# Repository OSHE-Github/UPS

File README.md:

# UPS

Uninterruptible Power Supply Hat for Raspberry Pi

This is still very early in the design phase and is not suitable for use.

*･゜ﾟ･*:.｡..｡.:*･'(*ﾟ▽ﾟ*)'･*:.｡. .｡.:*･゜ﾟ･*

## Copyright

- All code is licensed under the GPL 3.0 or later. You can view a copy of this license in LICENSE.code
- All hardware computer aided design "CAD files" are licensed under the CERN-OHL-S license. A copy of this license can be found in LICENSE.cad
- Some footprints are provided by the manufacturer or a third party source. They are licensed under their respective licenses.

Which licenses apply to which files will be clarified in a later commit. If you have questions please contact us.

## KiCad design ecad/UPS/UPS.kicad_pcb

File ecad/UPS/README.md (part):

## Current and thermal review - 2026-10-20

**The current board is not qualified for continuous 5 A USB output.** Two specified parts lack margin, and a single via carries the entire boost-input current. No PCB or firmware changes were made during this review.

The user confirmed the [GST36U12-P1J adapter](https://www.meanwell.com/Upload/PDF/GST36U/GST36U-SPEC.PDF): 12 V, 3 A, 36 W. Battery model remains unknown. The 5 A load is a review scenario, not a confirmed requirement. Calculations use the fitted boost divider's nominal 5.0895 V, 150 mA of provisional auxiliary load, 90% boost efficiency and 93% charger-stage efficiency. Efficiencies and auxiliary current must be measured. Voltages below refer to the boost input; battery-terminal voltage must be higher by the upstream drop. Four cells share current only approximately.

| Boost input | Input current at 3 A USB | Input current at 5 A USB |
| --- | ---: | ---: |
| 4.2 V | 4.24 A | 6.93 A |
| 3.7 V | 4.81 A | 7.87 A |
| 3.3 V | 5.40 A | 8.83 A |
| 3.0 V | 5.94 A | 9.71 A |

### Changes to prioritize

1. **R38:** the BOM's [RCL1218 jumper](https://www.vishay.com/docs/20046/rcle3.pdf) is rated 7 A, with resistance up to 20 milliohms. The 5 A USB scenario exceeds that at low battery. At 9.71 A, its resistance bound corresponds to 1.88 W; this is a sensitivity bound, not a measured loss. Replace it with a suitably rated low-resistance link or designed copper connection. Do not simply assume zero ohms means unlimited current.
2. **R38 copper escape:** a native connectivity experiment confirms that removing the single via at (133, 73) mm disconnects R38.1 from L2.1. Its drill is 0.3 mm, and its front trace is 0.8 mm wide / 1.4375 mm long. Provide a broad connection and a distributed via array when redesigning this feed. The other ten VIN vias do not bypass this bottleneck. [Evidence](review/current-path-bottleneck.json).
3. **F2:** the [MF-USML550/12](https://www.bourns.com/docs/product-datasheets/mf-usml-x.pdf) holds 5.5 A at 23 C, 4.68 A at 40 C, 4.15 A at 50 C and 3.6 A at 60 C. It carries USB plus auxiliary current. A 5 A USB load therefore lacks hot-enclosure margin. Select protection by hot hold-current, fault behavior and downstream ratings together; simply fitting a larger fuse is not a complete fix. F1 is also only 12 V rated, requiring voltage-margin review on the nominal 12 V adapter input.

### Where heat is likely

| Part / path | Calculation or observation | Review consequence |
| --- | --- | --- |
| R17 battery shunt | 0.94 W at 9.71 A with schematic 10 milliohms; 0.12 W with BOM 1.3 milliohms | Resolve the actual resistance, rating and footprint; these alternatives also change current measurement/control. |
| L2 boost inductor | About 0.51 W copper loss at 9.71 A using maximum 20 C DCR, before core loss and hot-resistance increase | Its published 16.8 A / 40 K-rise and 24.7 A / 30%-inductance-drop figures suggest current headroom; actual PCB temperature still needs testing. [Panasonic](https://na.industrial.panasonic.com/products/inductors-coils/surface-mount-power-inductors/lineup/power-inductors-automotive-applications/series/57509/model/70593). |
| PS1 boost stage | 2.91 W total converter loss at 90% efficiency, versus 1.38 W at 95%, at the provisional 5 A load | This includes L2 and other converter losses; it is not all IC heat. Do not add L2 loss to it again. |
| Q4 battery FET | At 9.71 A, every 10 milliohms produces 0.94 W | Its resistance needs actual gate drive and hot-junction characterization. The FDS6681Z guarantees quoted on-resistance at -4.5/-10 V gate drive; do not assume those numbers at low 1S voltage. [onsemi](https://www.onsemi.com/download/data-sheet/pdf/fds6681z-d.pdf). |
| Q3 USB switch | 5 A through 4 milliohms is 0.10 W at the datasheet's 4.5 V gate-drive condition | Verify gate overdrive and hot resistance; not currently the leading estimated heater. [Infineon](https://www.infineon.com/assets/row/public/documents/24/49/infineon-irlr7843-datasheet-en.pdf). |
| L1 charger inductor | Published 12 A RMS at 40 C rise, 27 A saturation criterion, 7 milliohm maximum DCR | It carries system current plus charge current on adapter power. A 36 W / 93% / 3 V limiting scenario is 11.16 A and about 0.87 W DC copper loss before ripple/core loss. Use actual VSYS setting, not battery voltage, for final sizing. Footprint compatibility remains unresolved. [Bourns](https://www.bourns.com/docs/product-datasheets/srp1038a.pdf). |

At the 5 A scenario, the adapter supplies approximately **2.61 A before charging**, leaving an upper estimate of **4.36 W** on the system rail for charging, before charge-path loss and design reserve. That is about 1 A charging near 4.2 V. Charge-current control must yield to the 3 A input limit. The firmware inspected currently handles battery voltage and fan control; this review did not find a complete charging/temperature-shutdown policy in the production main loop.

### Temperature and copper limits

The [TPS61288 datasheet](https://www.ti.com/lit/ds/symlink/tps61288.pdf) specifies a 125 C recommended junction maximum and reports 33.6 C/W on its EVM versus 71.4 C/W on its standard test board. At 40 C ambient and 1 W IC dissipation these give 74 C versus 111 C; at 1.5 W they give 90 C versus 147 C. These are sensitivity examples, not predictions for this PCB or certification of the selected L variant. The 15 A headline is peak switch current, not available USB output current; its current-limit table is characterized under different voltage conditions.

The saved stackup specifies approximately 2 oz outer copper and 0.5 oz inner copper. Confirm these with the fabricator. Broad outer pours help, but neither connectivity nor via count establishes temperature rise. The one via's resistance is approximately 1.2 milliohms if its barrel has 25 um copper over 1.634 mm; that is about 0.11 W at 9.71 A. Plating thickness is an assumption, and this does not predict via temperature. Q4 and PS1 need local spreading/airflow review; the battery holders beneath the board can obstruct cooling.

Upstream voltage drop increases current: with 3.0 V at the battery and the same 5 A load, illustrative total pre-boost resistances of 20 and 40 milliohms require about 10.43 and 11.46 A, respectively, instead of 9.71 A. These resistances are sensitivity cases, not measured board values. They exclude the converter loss already represented by efficiency.

### Validation still needed

Resolve R38, F2 and the shunts before a full-load test. Then use a current-limited battery simulator and electronic load to sweep 1/2/3 A and only proceed to 5 A after the revised ratings permit it. Test adapter-only, battery-only, switchover and simultaneous charging at the intended minimum cell voltage. Log USB voltage at the load, battery current, voltage drops across R17/R38/F2, and temperatures at PS1, Q4, L1/L2, shunts, fuse and the via transition until stable. Repeat with the real enclosure and intended ambient/airflow. The existing fan's 40 C-on / 35 C-off policy is cooling control, not battery temperature protection. Cell-specific charge/discharge limits, current capability, cutoff voltage and holder/contact heating remain open until the cell model is identified.

Calculation evidence: [20 load/voltage scenarios](review/current-thermal-scenarios.csv), [assumptions and sources](review/current-thermal-review.json). Estimates are a design screen, not a thermal simulation or load-test result.

---

## Latest fabrication review - 2026-10-20

**Not ready for fabrication.** This section supersedes the historical status/counts below.

Corrected three electrical faults: R26's isolated GNDA return now joins GND; C9 is 470nF (formerly 470pF); unused STM32 VLCD pin 1 now joins the VDDA/+3.3V rail. Sources and procurement implications are recorded in [fab-findings.csv](review/fab-findings.csv). The raw supplied BOM is preserved; it must not be used as a released purchasing list yet.

After native zone refill: **0 unconnected items, 0 shorts/clearance/drill/keepout/thermal-connection errors, and 0 schematic/PCB parity issues**. All 85 populated nets connect, all 504 previous numbered-pad memberships and every existing track remain preserved, and all 14 main power terminal groups pass the separate connectivity check. Footprint positions, packages, project rules, bottom-edge controls and underside connector arrangement are unchanged. The two deliberate net merges are recorded in approved-net-changes.json; C9 is the only component-value change in this pass.

**Release blockers:** R11/R17 10mOhm schematic versus 1.3mOhm BOM and shunt land-pattern mismatch; D3/D4 3.5V intent versus 51V-standoff BOM; L1 manufacturer/footprint compatibility; missing explicit STM bulk/analog decoupling; replacement connector and actual-part selection. Confirm cell model, adapter voltage/current and maximum 5V load before current/thermal review. Mount-hole geometry is checked, but enclosure, component heights and cable access are not physically verified.

**Remaining native findings:** 164 PCB findings (44 footprint-library mismatches, 4 malformed courtyards, 116 silkscreen/text findings), and 124 schematic ERC findings (44 errors, 80 warnings). Imported symbol types explain some ERC reports, but these have not been blanket-waived. A clean copper-routing result is not a fabrication signoff.

Evidence: [fab-review.json](review/fab-review.json), [fab-findings.csv](review/fab-findings.csv), [fab-final-drc.json](review/fab-final-drc.json), [fab-final-erc.json](review/fab-final-erc.json), and [validation-summary.json](review/validation-summary.json). Backup: C:/Users/john/.codex/backups/UPS/2026-10-20-fab-checks/. Re-run tools/verify_candidate.py after refreshing native evidence for future edits.

---

## Current control-layout checkpoint - 2026-10-20

The MCU/control routing has been rebuilt and all existing electrical nets are now connected: **0 unconnected items**. U4 remains at (101, 142) mm. The temperature-input resistor/capacitor pairs, MCU bypass capacitors, LED row, and boot/reset controls are grouped. RESET and BOOT are together near the bottom edge, with three optional GPIO-button locations reserved on Dwgs.User; no new switches or GPIO circuits were added.

Only J2/J5/J6/J11 were moved to B.Cu, into the channels between the battery holders. All temperature-input resistors and capacitors remain on F.Cu. Existing thermistor connector footprints are placeholders until replacement parts are selected; recheck the actual housing and mating-cable clearance when they are chosen.

Corrected two controller power-symbol values from 3.3V to +3.3V, joining C61.2, R29.1 and U6.2 to the regulator supply. This is the only schematic connectivity change in this pass. All 472 previously connected pad memberships remain connected; all 86 populated electrical nets, all 31 BQ nets, all 19 USB-related nets and all 14 main-power path audits pass.

Native DRC has zero shorts, copper clearances, drill conflicts, keepout violations, courtyard overlaps, incomplete thermal connections, dangling tracks/vias, or schematic parity issues. **164 other findings remain**: 44 library-footprint mismatches, 4 malformed courtyards, 48 silk-over-copper, 62 silk overlaps, 5 text-height and 1 silk-edge finding. These and the outstanding BOM/land-pattern/current/thermal review below still need resolution before fabrication.

Current evidence: [controls-cleanup.json](review/controls-cleanup.json), [controls-cleanup-drc.json](review/controls-cleanup-drc.json), [validation-summary.json](review/validation-summary.json). Pre-cleanup board: C:/Users/john/.codex/backups/UPS/2026-10-20-controls-cleanup/before.kicad_pcb; original controller schematic: original-controller.kicad_sch in that directory.

[Front controls preview](review/controls-front.png) | [Battery-side connector preview](review/controls-back.png)

Earlier sections below retain historical checkpoint counts.

---

# UPS ground, power and USB-C checkpoint

Continue in **ecad/UPS/UPS.kicad_pro**, using the single active **UPS.kicad_pcb** on branch **codex/placement-optimization**. The team baseline remains on **newmain**, commit `f5ad96ca7c6ce8b75538aafb6f14a27db1c61da7`. Close KiCad before switching branches, then reopen this same project.

The saved board now connects the grounds, charger bridge, battery bus, charger-to-boost feed, and boost-to-fuse-to-USB power path. Charger gate, bootstrap, sensing and supply connections are routed. The USB-C connector, protection, controller support and MCU control links are now routed as well. **47 unconnected items remain elsewhere; this is an unfinished board.** The input-current, battery-current, thermal and EMI limits have not been validated.

This preview uses actual filled copper and pad geometry. It crops the upper board and shows both layers from the top. Grey copper is ground; the other colours distinguish the main rails. The inner ground reference is not pictured. The battery-positive bus crosses the bottom of the crop.

## What changed on 20 October 2026

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
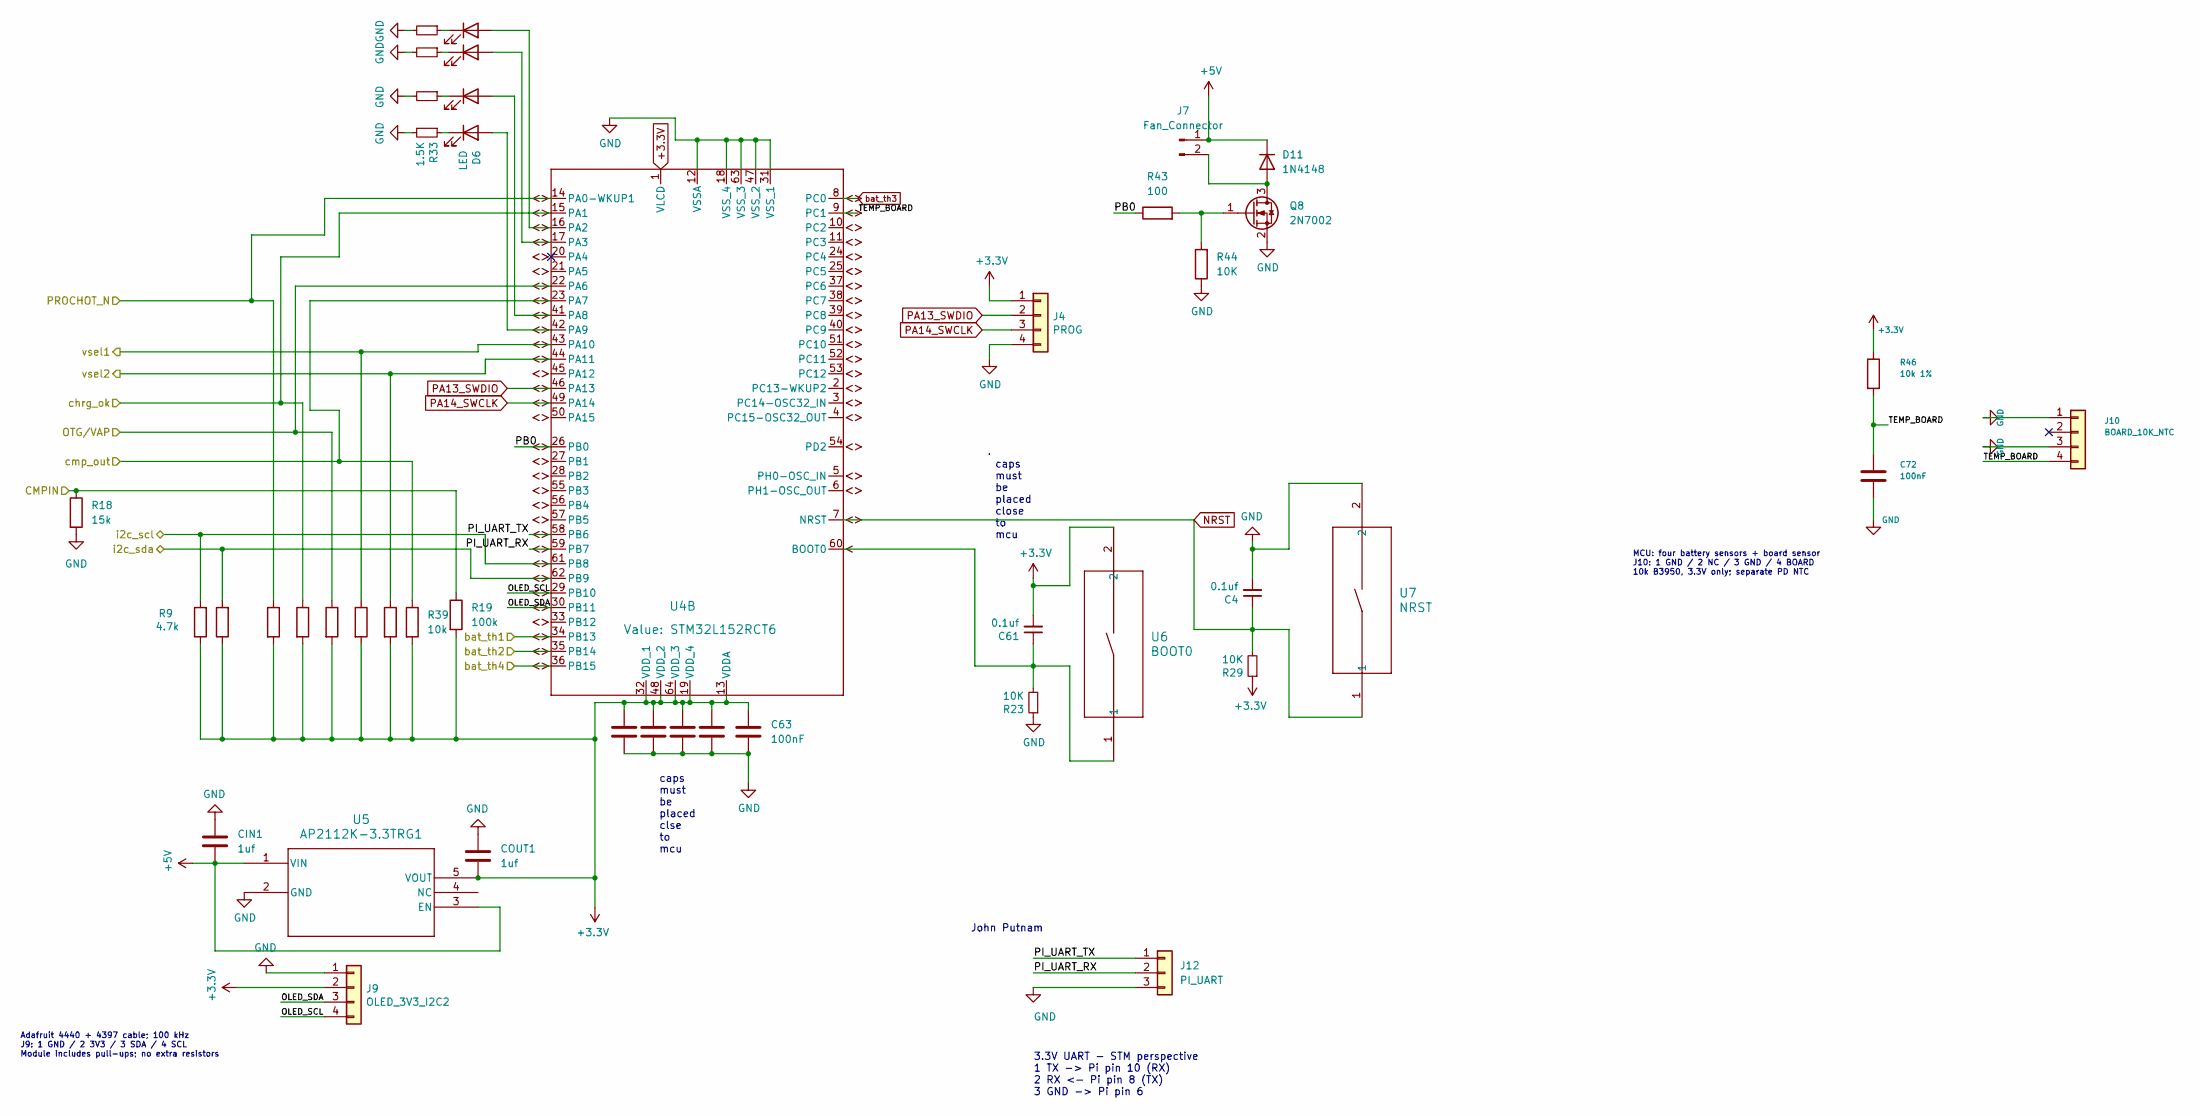
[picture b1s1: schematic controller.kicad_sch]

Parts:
C4, C61: 0.1uf; C_0603_1608Metric; MPN C0603C104K4RACTU; Mouser 80-C0603C104K4R
C27, C49, C50, C62, C63, C72: 100nF; C_0805_2012Metric
CIN1: 1uf; C_0805_2012Metric
COUT1: 1uf; C_0805_2012Metric
D6, D8, D9, D10: LED; LED_0805_2012Metric; MPN AP2012HD; Mouser 604-AP2012HD
D11: 1N4148; D_DO-35_SOD27_P7.62mm_Horizontal
J4: PROG; PinHeader_1x04_P2.54mm_Vertical
J7: Fan_Connector; LED_D5.0mm_IRGrey
J9: OLED_3V3_I2C2; PinHeader_1x04_P2.54mm_Vertical
J10: BOARD_10K_NTC; PinHeader_1x04_P2.54mm_Vertical
J12: PI_UART; PinHeader_1x03_P2.54mm_Vertical
Q8: 2N7002; SOT-23
R9, R10: 4.7k; R_0805_2012Metric
R12, R15, R16, R36, R37, R39: 10k; R_0805_2012Metric
R18: 15k; R_0805_2012Metric
R19: 100k; R_0805_2012Metric
R20, R21, R22, R33: 1.5K; R_0805_2012Metric; MPN RCC08051K50FKEA; Mouser 71-RCC08051K50FKEA
R23, R29: 10K; R_0805_2012Metric; MPN CR0805-FX-1002ELF; Mouser 652-CR0805FX-1002ELF
R43: 100; R_0603_1608Metric
R44: 10K; R_0603_1608Metric_Pad0.98x0.95mm_HandSolder
R46: 10k 1%; R_0805_2012Metric
U4: STM32L152RCT6; LQFP64-10x10mm
U5: AP2112K-3.3TRG1; SOT_RG1_DIO
U6: BOOT0; B3U-1000P-B
U7: NRST; B3U-1000P-B

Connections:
+3.3V: C27.2, C49.2, C50.2, C61.2, C62.2, C63.2, COUT1.1, J4.1, J9.2, R9.1, R10.1, R12.2, R15.2, R16.2, R19.2, R29.1, R36.2, R37.2, R39.2, R46.1, U4.1 (VLCD), U4.13 (VDDA), U4.19 (VDD_4), U4.32 (VDD_1), U4.48 (VDD_2), U4.64 (VDD_3), U5.5 (VOUT), U6.2; also elsewhere on the board
+5V: CIN1.1, D11.1 (K), J7.1, U5.1 (VIN), U5.3 (EN); also elsewhere on the board
/Charger/CMPIN: R18.1, R19.1; also elsewhere on the board
/Charger/OTG/VAP: R16.1, U4.22 (PA6); also elsewhere on the board
/Charger/PROCHOT_N: R12.1, U4.14 (PA0-WKUP1); also elsewhere on the board
/Charger/bat_th1: U4.34 (PB13); also elsewhere on the board
/Charger/bat_th2: U4.35 (PB14); also elsewhere on the board
/Charger/bat_th4: U4.36 (PB15); also elsewhere on the board
/Charger/chrg_ok: R15.1, U4.15 (PA1); also elsewhere on the board
/Charger/cmp_out: R39.1, U4.23 (PA7); also elsewhere on the board
/Output/SCL: R9.2, U4.61 (PB8); also elsewhere on the board
/Output/SDA: R10.2, U4.62 (PB9); also elsewhere on the board
/Output/vsel1: R36.1, U4.43 (PA10); also elsewhere on the board
/Output/vsel2: R37.1, U4.44 (PA11); also elsewhere on the board
/controller/OLED_SCL: J9.4, U4.29 (PB10)
/controller/OLED_SDA: J9.3, U4.30 (PB11)
/controller/PB0: R43.1, U4.26 (PB0)
/controller/PI_UART_RX: J12.2, U4.59 (PB7)
/controller/PI_UART_TX: J12.1, U4.58 (PB6)
/controller/TEMP_BOARD: C72.1, J10.4, R46.2, U4.9 (PC1)
GND: C4.2, C27.1, C49.1, C50.1, C62.1, C63.1, C72.2, CIN1.2, COUT1.2, J4.4, J9.1, J10.1, J10.3, J12.3, Q8.2 (S), R18.2, R20.2, R21.2, R22.2, R23.1, R33.2, R44.1, U4.12 (VSSA), U4.18 (VSS_4), U4.31 (VSS_1), U4.47 (VSS_2), U4.63 (VSS_3), U5.2 (GND), U7.2; also elsewhere on the board
NRST: C4.1, R29.2, U4.7 (NRST), U7.1
unnamed: D6.2 (A), U4.42 (PA9)
unnamed: D6.1 (K), R33.1
unnamed: D8.2 (A), U4.16 (PA2)
unnamed: D8.1 (K), R20.1
unnamed: D9.2 (A), U4.17 (PA3)
unnamed: D9.1 (K), R21.1
unnamed: D10.2 (A), U4.41 (PA8)
unnamed: D10.1 (K), R22.1
unnamed: D11.2 (A), J7.2, Q8.3 (D)
unnamed: Q8.1 (G), R43.2, R44.2
unnamed: C61.1, R23.2, U4.60 (BOOT0), U6.1
PA13_SWDIO: J4.2, U4.46 (PA13)
PA14_SWCLK: J4.3, U4.49 (PA14)
bat_th3: U4.8 (PC0); also elsewhere on the board

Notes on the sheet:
John Putnam
3.3V UART - STM perspective 1 TX -> Pi pin 10 (RX) 2 RX <- Pi pin 8 (TX) 3 GND -> Pi pin 6
Adafruit 4440 + 4397 cable; 100 kHz J9: 1 GND / 2 3V3 / 3 SDA / 4 SCL Module includes pull-ups; no extra resistors
MCU: four battery sensors + board sensor J10: 1 GND / 2 NC / 3 GND / 4 BOARD 10k B3950, 3.3V only; separate PD NTC
caps must be placed clse to mcu
caps must be placed close to mcu

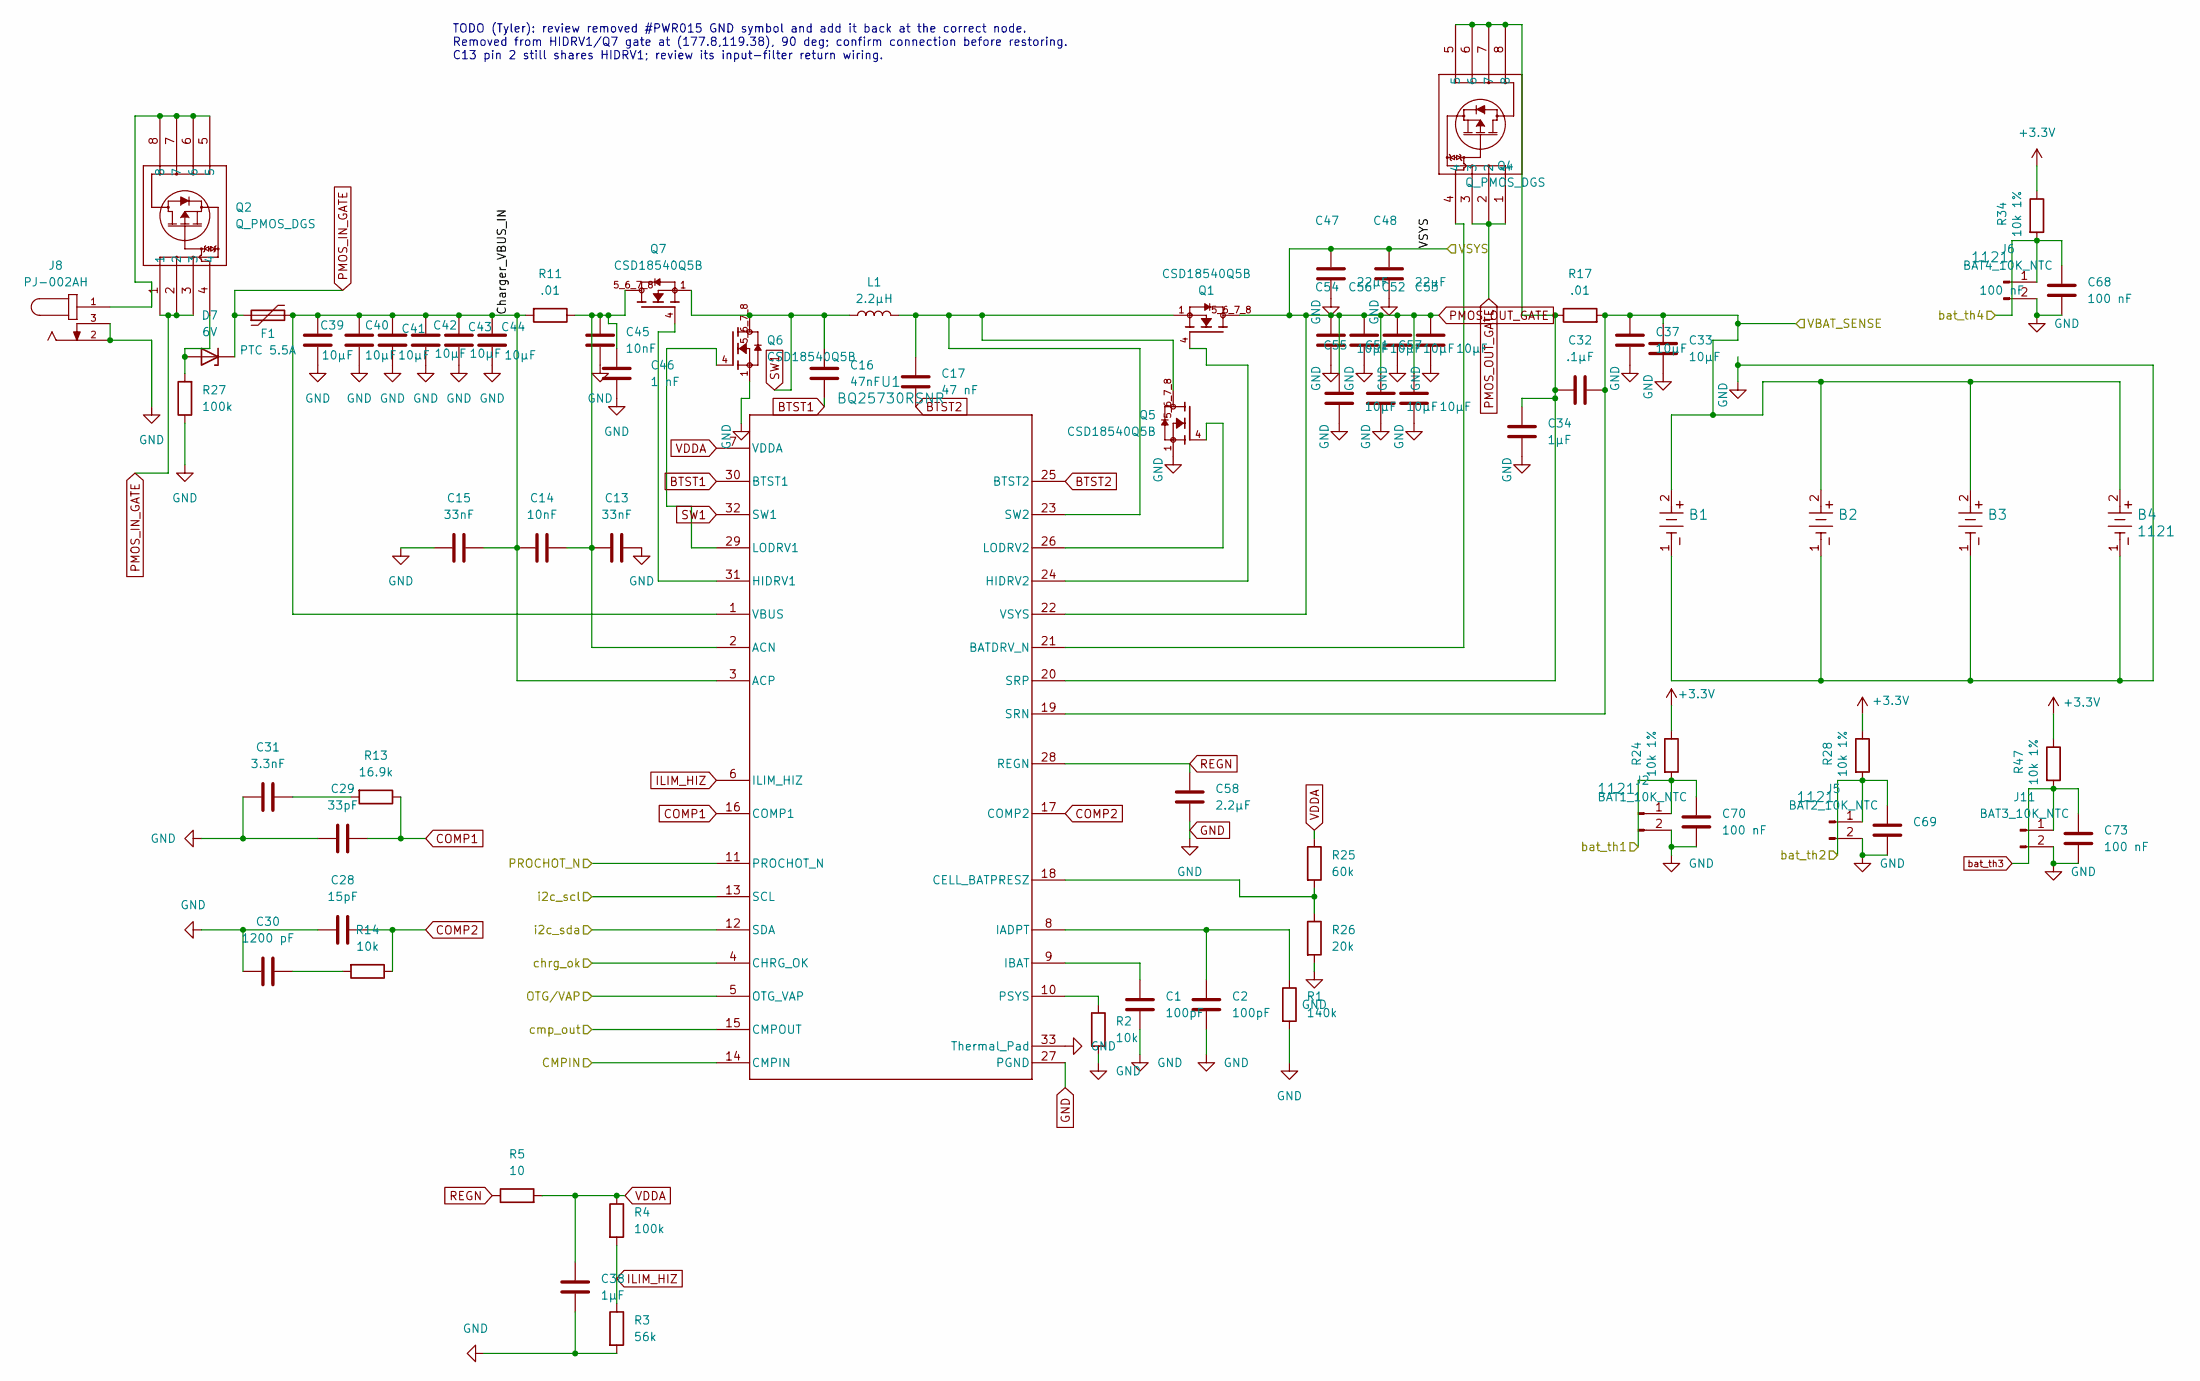
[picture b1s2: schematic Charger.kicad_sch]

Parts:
B1, B2, B3, B4: 1121; 1121_KEY
C1, C2: 100pF; C_0603_1608Metric
C13, C15: 33nF; C_0603_1608Metric
C14, C45: 10nF; C_0603_1608Metric
C16: 47nF; C_0603_1608Metric
C17: 47 nF; C_0603_1608Metric
C28: 15pF; C_0603_1608Metric
C29: 33pF; C_0603_1608Metric
C30: 1200 pF; C_0603_1608Metric
C31: 3.3nF; C_0603_1608Metric
C32: .1µF; C_0603_1608Metric
C33, C37: 10µF; C_0603_1608Metric
C34, C38: 1µF; C_0603_1608Metric
C39, C40, C41, C42, C43, C44: 10µF; C_1210_3225Metric
C46: 1 nF; C_0603_1608Metric
C47, C48: 22µF; C_1206_3216Metric
C51, C52, C53, C54, C55, C56, C57: 10µF; C_0805_2012Metric
C58: 2.2µF; C_0603_1608Metric
C68, C69, C70, C73: 100 nF; C_0603_1608Metric
D7: 6V; D_SMB_Handsoldering
F1: PTC 5.5A; Fuse_1210_3225Metric_Pad1.42x2.65mm_HandSolder
J2: BAT1_10K_NTC; JST_XH_B2B-XH-A_1x02_P2.50mm_Vertical
J5: BAT2_10K_NTC; JST_XH_B2B-XH-A_1x02_P2.50mm_Vertical
J6: BAT4_10K_NTC; JST_XH_B2B-XH-A_1x02_P2.50mm_Vertical
J8: PJ-002AH; CUI_PJ-002AH
J11: BAT3_10K_NTC; JST_XH_B2B-XH-A_1x02_P2.50mm_Vertical
L1: 2.2µH; L_Vishay_IHLP-4040
Q1, Q5, Q6, Q7: CSD18540Q5B; TRANS_CSD18540Q5B; PARTREV B; DigiKey_Part_Number 296-41076-1-ND
Q2: Q_PMOS_DGS; FDS6681Z_OSI-M
Q4: Q_PMOS_DGS; FDS6681Z_OSI
R1: 140k; R_0805_2012Metric
R2, R14: 10k; R_0805_2012Metric
R3: 56k; R_0805_2012Metric
R4, R27: 100k; R_0805_2012Metric
R5: 10; R_0805_2012Metric
R11, R17: .01; R_2512_6332Metric
R13: 16.9k; R_0805_2012Metric
R24, R28, R34, R47: 10k 1%; R_0805_2012Metric_Pad1.20x1.40mm_HandSolder
R25: 60k; R_0805_2012Metric
R26: 20k; R_0805_2012Metric
U1: BQ25730RSNR; Texas_RSN_WQFN-32-1EP_4x4mm_P0.4mm_EP2.8x2.8mm

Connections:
+3.3V: R24.1, R28.1, R34.1, R47.1; also elsewhere on the board
/Charger/CMPIN: U1.14 (CMPIN); also elsewhere on the board
/Charger/Charger_VBUS_IN: C14.1, C15.2, C39.1, C40.1, C41.1, C42.1, C43.1, C44.1, F1.2, R11.2, U1.1 (VBUS), U1.3 (ACP)
/Charger/OTG/VAP: U1.5 (OTG_VAP); also elsewhere on the board
/Charger/PROCHOT_N: U1.11 (PROCHOT_N); also elsewhere on the board
/Charger/VBAT_SENSE: B1.2, B2.2, B3.2, B4.2, C32.1, C33.1, C37.1, R17.2, U1.19 (SRN); also elsewhere on the board
/Charger/bat_th1: C70.1, J2.1, R24.2; also elsewhere on the board
/Charger/bat_th2: C69.1, J5.1, R28.2; also elsewhere on the board
/Charger/bat_th4: C68.1, J6.1, R34.2; also elsewhere on the board
/Charger/chrg_ok: U1.4 (CHRG_OK); also elsewhere on the board
/Charger/cmp_out: U1.15 (CMPOUT); also elsewhere on the board
/Output/SCL: U1.13 (SCL); also elsewhere on the board
/Output/SDA: U1.12 (SDA); also elsewhere on the board
BTST1: C16.1, U1.30 (BTST1)
BTST2: C17.1, U1.25 (BTST2)
COMP1: C29.2, R13.1, U1.16 (COMP1)
COMP2: C28.2, R14.1, U1.17 (COMP2)
GND: B1.1, B2.1, B3.1, B4.1, C1.2, C2.2, C13.2, C15.1, C28.1, C29.1, C30.1, C31.1, C33.2, C34.2, C37.2, C38.2, C39.2, C40.2, C41.2, C42.2, C43.2, C44.2, C45.2, C46.2, C47.2, C48.2, C51.2, C52.2, C53.2, C54.2, C55.2, C56.2, C57.2, C58.2, C68.2, C69.2, C70.2, C73.2, J2.2, J5.2, J6.2, J8.2, J8.3, J11.2, Q5.1, Q5.2, Q5.3, Q6.1, Q6.2, Q6.3, R1.2, R2.2, R3.2, R26.2, R27.1, U1.27 (PGND), U1.33 (Thermal_Pad); also elsewhere on the board
ILIM_HIZ: R3.1, R4.2, U1.6 (ILIM_HIZ)
unnamed: C30.2, R14.2
unnamed: C31.2, R13.2
unnamed: D7.2 (A), Q2.4, R27.2
unnamed: J8.1, Q2.5, Q2.6, Q2.7, Q2.8
unnamed: C13.1, C14.2, C45.1, C46.1, Q7.5_6_7_8, R11.1, U1.2 (ACN)
unnamed: Q4.4, U1.21 (BATDRV_N)
unnamed: R25.2, R26.1, U1.18 (CELL_BATPRESZ)
unnamed: Q7.4, U1.31 (HIDRV1)
unnamed: Q1.4, U1.24 (HIDRV2)
unnamed: C2.1, R1.1, U1.8 (IADPT)
unnamed: C1.1, U1.9 (IBAT)
unnamed: Q6.4, U1.29 (LODRV1)
unnamed: Q5.4, U1.26 (LODRV2)
unnamed: R2.1, U1.10 (PSYS)
unnamed: C32.2, C34.1, Q4.5, Q4.6, Q4.7, Q4.8, R17.1, U1.20 (SRP)
unnamed: C17.2, L1.2, Q1.1, Q1.2, Q1.3, Q5.5_6_7_8, U1.23 (SW2)
PMOS_IN_GATE: D7.1 (K), F1.1, Q2.1, Q2.2, Q2.3
PMOS_OUT_GATE: C47.1, C48.1, C51.1, C52.1, C53.1, C54.1, C55.1, C56.1, C57.1, Q1.5_6_7_8, Q4.1, Q4.2, Q4.3, U1.22 (VSYS); also elsewhere on the board
REGN: C58.1, R5.1, U1.28 (REGN)
SW1: C16.2, L1.1, Q6.5_6_7_8, Q7.1, Q7.2, Q7.3, U1.32 (SW1)
VDDA: C38.1, R4.1, R5.2, R25.1, U1.7 (VDDA)
bat_th3: C73.1, J11.1, R47.2; also elsewhere on the board

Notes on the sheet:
TODO (Tyler): review removed #PWR015 GND symbol and add it back at the correct node. Removed from HIDRV1/Q7 gate at (177.8,119.38), 90 deg; confirm connection before restoring. C13 pin 2 still shares HIDRV1; review its input-filter return wiring.

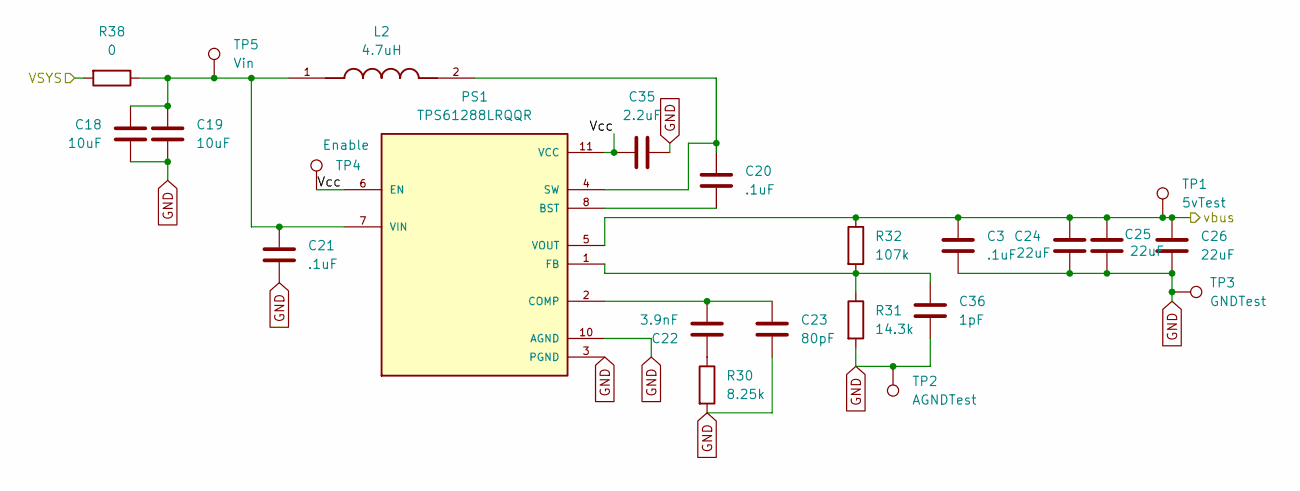
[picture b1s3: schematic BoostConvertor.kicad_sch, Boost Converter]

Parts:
C3, C20, C21: .1uF; C_0603_1608Metric_Pad1.08x0.95mm_HandSolder
C18, C19: 10uF; C_0805_2012Metric_Pad1.18x1.45mm_HandSolder
C22: 3.9nF; C_0603_1608Metric_Pad1.08x0.95mm_HandSolder
C23: 80pF; C_0603_1608Metric_Pad1.08x0.95mm_HandSolder
C24, C25, C26: 22uF; C_0805_2012Metric_Pad1.18x1.45mm_HandSolder
C35: 2.2uF; C_0603_1608Metric_Pad1.08x0.95mm_HandSolder
C36: 1pF; C_0603_1608Metric_Pad1.08x0.95mm_HandSolder
L2: 4.7uH; IND_ETQP8M4R7JFA; PARTREV 1-Feb-20
PS1: TPS61288LRQQR; CONV_TPS61288LRQQR; PARTREV C
R30: 8.25k; R_0603_1608Metric_Pad0.98x0.95mm_HandSolder
R31: 14.3k; R_0603_1608Metric_Pad0.98x0.95mm_HandSolder
R32: 107k; R_0603_1608Metric_Pad0.98x0.95mm_HandSolder
R38: 0; R_1218_3246Metric_Pad1.22x4.75mm_HandSolder
TP1: 5vTest; TestPoint_Pad_D1.5mm
TP2: AGNDTest; TestPoint_Pad_D1.5mm
TP3: GNDTest; TespointBig
TP4: Enable; TestPoint_Pad_D1.5mm
TP5: Vin; TespointBig

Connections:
/BoostConvertor/Vcc: C35.1, PS1.6 (EN), PS1.11 (VCC), TP4.1 (1_1)
/BoostConvertor/vbus: C3.1, C24.1, C25.1, C26.1, PS1.5 (VOUT), R32.1, TP1.1 (1_1); also elsewhere on the board
GND: C3.2, C18.2, C19.2, C21.2, C23.2, C24.2, C25.2, C26.2, C35.2, C36.2, PS1.3 (PGND), PS1.10 (AGND), R30.2, R31.2, TP2.1 (1_1), TP3.1 (1_1); also elsewhere on the board
unnamed: C20.1, L2.2, PS1.4 (SW), PS1.9 (SW)
unnamed: C22.1, R30.1
unnamed: C20.2, PS1.8 (BST)
unnamed: C22.2, C23.1, PS1.2 (COMP)
unnamed: C36.1, PS1.1 (FB), R31.1, R32.2
unnamed: C18.1, C19.1, C21.1, L2.1, PS1.7 (VIN), R38.1, TP5.1 (1_1)
PMOS_OUT_GATE: R38.2; also elsewhere on the board

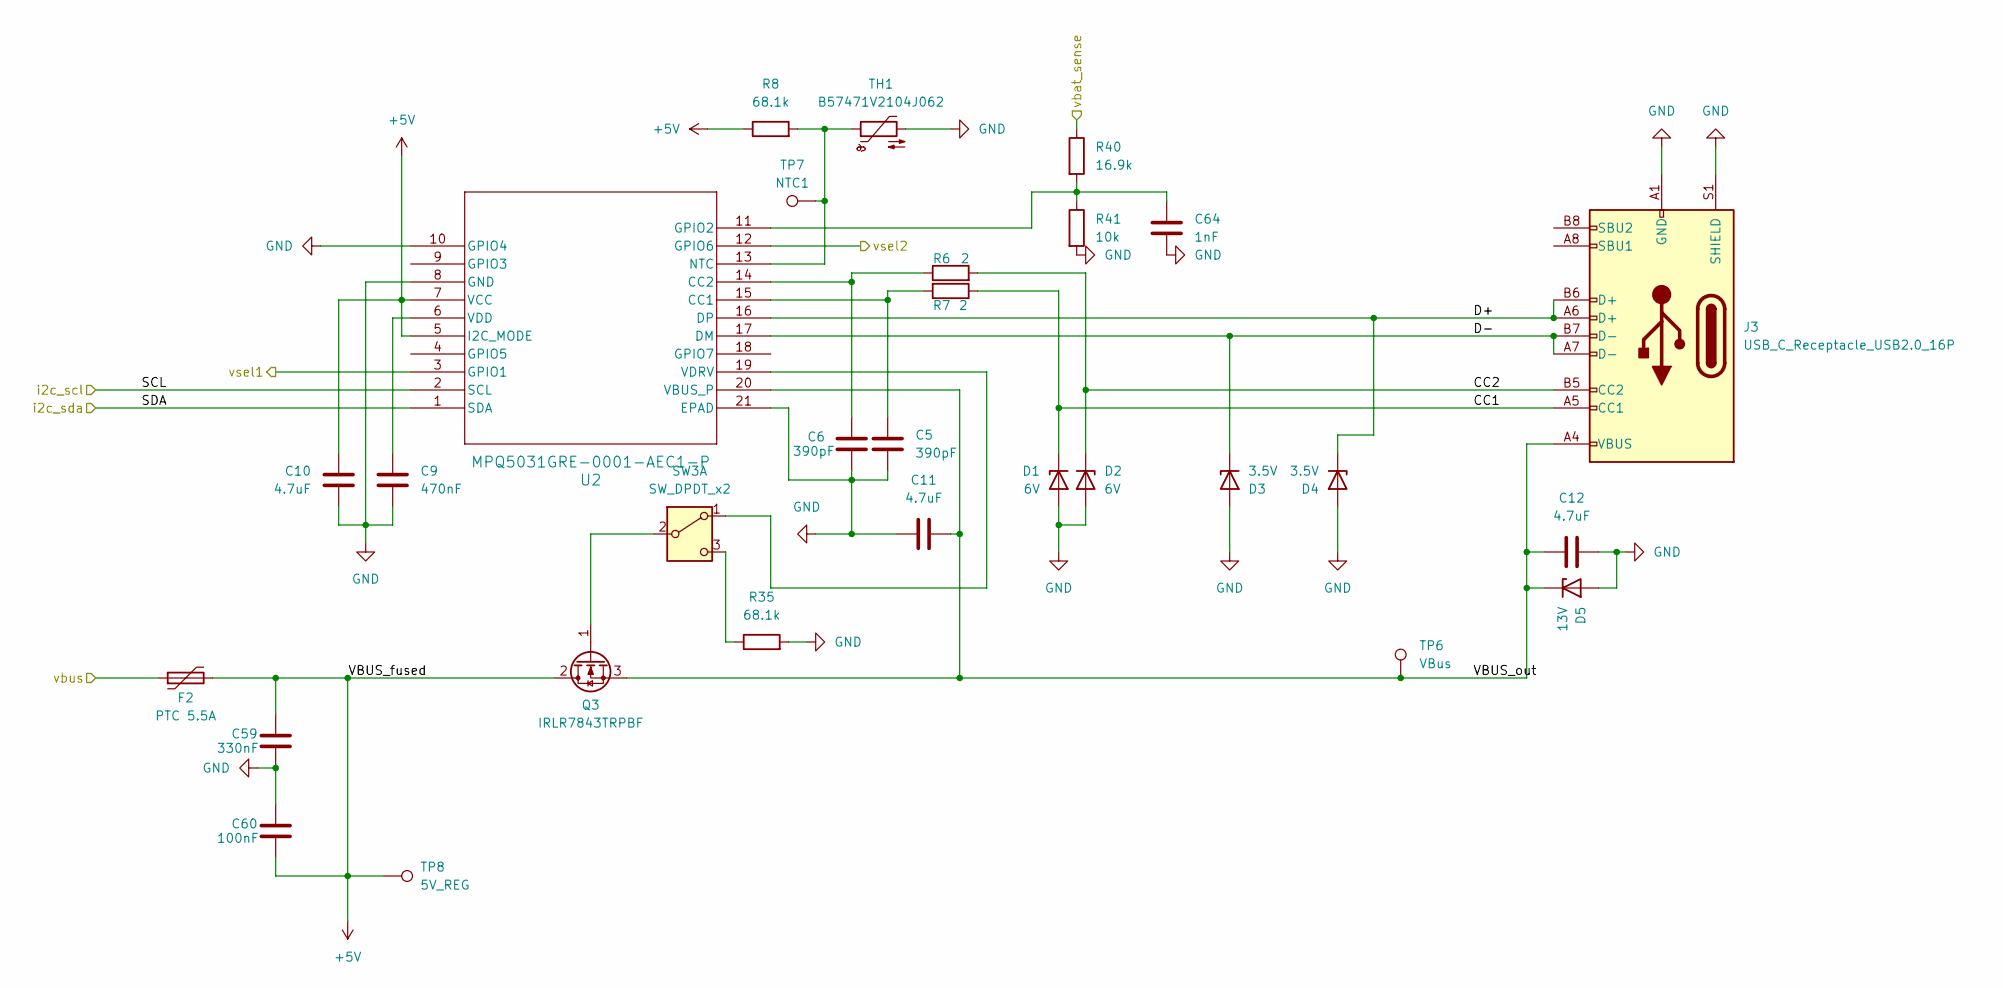
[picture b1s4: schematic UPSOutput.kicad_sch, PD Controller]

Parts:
C5, C6: 390pF; C_0603_1608Metric_Pad1.08x0.95mm_HandSolder
C9: 470nF; C_0603_1608Metric_Pad1.08x0.95mm_HandSolder
C10, C11, C12: 4.7uF; C_0805_2012Metric_Pad1.18x1.45mm_HandSolder
C59: 330nF; C_0603_1608Metric_Pad1.08x0.95mm_HandSolder
C60: 100nF; C_0805_2012Metric_Pad1.18x1.45mm_HandSolder
C64: 1nF; C_0603_1608Metric_Pad1.08x0.95mm_HandSolder
D1, D2: 6V; D_SMB_Handsoldering
D3, D4: 3.5V; D_SMB_Handsoldering
D5: 13V; D_SMB_Handsoldering
F2: PTC 5.5A; Fuse_1210_3225Metric_Pad1.42x2.65mm_HandSolder
J3: USB_C_Receptacle_USB2.0_16P; USB_C_Receptacle_GCT_USB4110
Q3: IRLR7843TRPBF; TO-252-2
R6, R7: 2; R_1206_3216Metric_Pad1.30x1.75mm_HandSolder
R8, R35: 68.1k; R_0805_2012Metric_Pad1.20x1.40mm_HandSolder
R40: 16.9k; R_0603_1608Metric_Pad0.98x0.95mm_HandSolder
R41: 10k; R_0603_1608Metric_Pad0.98x0.95mm_HandSolder
SW3: SW_DPDT_x2; SW_EG1218
TH1: B57471V2104J062; R_0805_2012Metric_Pad1.20x1.40mm_HandSolder
TP6: VBus; TestPoint_Pad_D1.5mm
TP7: NTC1; TestPoint_Pad_D1.5mm
TP8: 5V_REG; TestPoint_Pad_D1.5mm
U2: MPQ5031GRE-0001-AEC1-P; QFN-20_MPQ5031_MNP

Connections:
+5V: C10.1, C59.1, C60.2, F2.2, Q3.2 (D), R8.1, TP8.1 (1_1), U2.5 (I2C_MODE), U2.7 (VCC); also elsewhere on the board
/BoostConvertor/vbus: F2.1; also elsewhere on the board
/Charger/VBAT_SENSE: R40.1; also elsewhere on the board
/Output/CC1: D1.1 (K), J3.A5 (CC1), R7.1
/Output/CC2: D2.1 (K), J3.B5 (CC2), R6.2
/Output/D+: D4.1 (K), J3.A6 (D+), J3.B6 (D+), U2.16 (DP)
/Output/D-: D3.1 (K), J3.A7 (D-), J3.B7 (D-), U2.17 (DM)
/Output/SCL: U2.2 (SCL); also elsewhere on the board
/Output/SDA: U2.1 (SDA); also elsewhere on the board
/Output/VBUS_out: C11.2, C12.1, D5.1 (K), J3.A4 (VBUS), J3.A9 (VBUS), J3.B4 (VBUS), J3.B9 (VBUS), Q3.3 (S), TP6.1 (1_1), U2.20 (VBUS_P)
/Output/vsel1: U2.3 (GPIO1); also elsewhere on the board
/Output/vsel2: U2.12 (GPIO6); also elsewhere on the board
GND: C5.2, C6.2, C9.2, C10.2, C11.1, C12.2, C59.2, C60.1, C64.2, D1.2 (A), D2.2 (A), D3.2 (A), D4.2 (A), D5.2 (A), J3.A1 (GND), J3.A12 (GND), J3.B1 (GND), J3.B12 (GND), J3.S1 (SHIELD), R35.2, R41.2, TH1.2, U2.8 (GND), U2.10 (GPIO4), U2.21 (EPAD); also elsewhere on the board
unnamed: Q3.1 (G), SW3.2 (B)
unnamed: SW3.1 (A), U2.19 (VDRV)
unnamed: R35.1, SW3.3 (C)
unnamed: C5.1, R7.2, U2.15 (CC1)
unnamed: C6.1, R6.1, U2.14 (CC2)
unnamed: C64.1, R40.2, R41.1, U2.11 (GPIO2)
unnamed: R8.2, TH1.1, TP7.1 (1_1), U2.13 (NTC)
unnamed: C9.1, U2.6 (VDD)

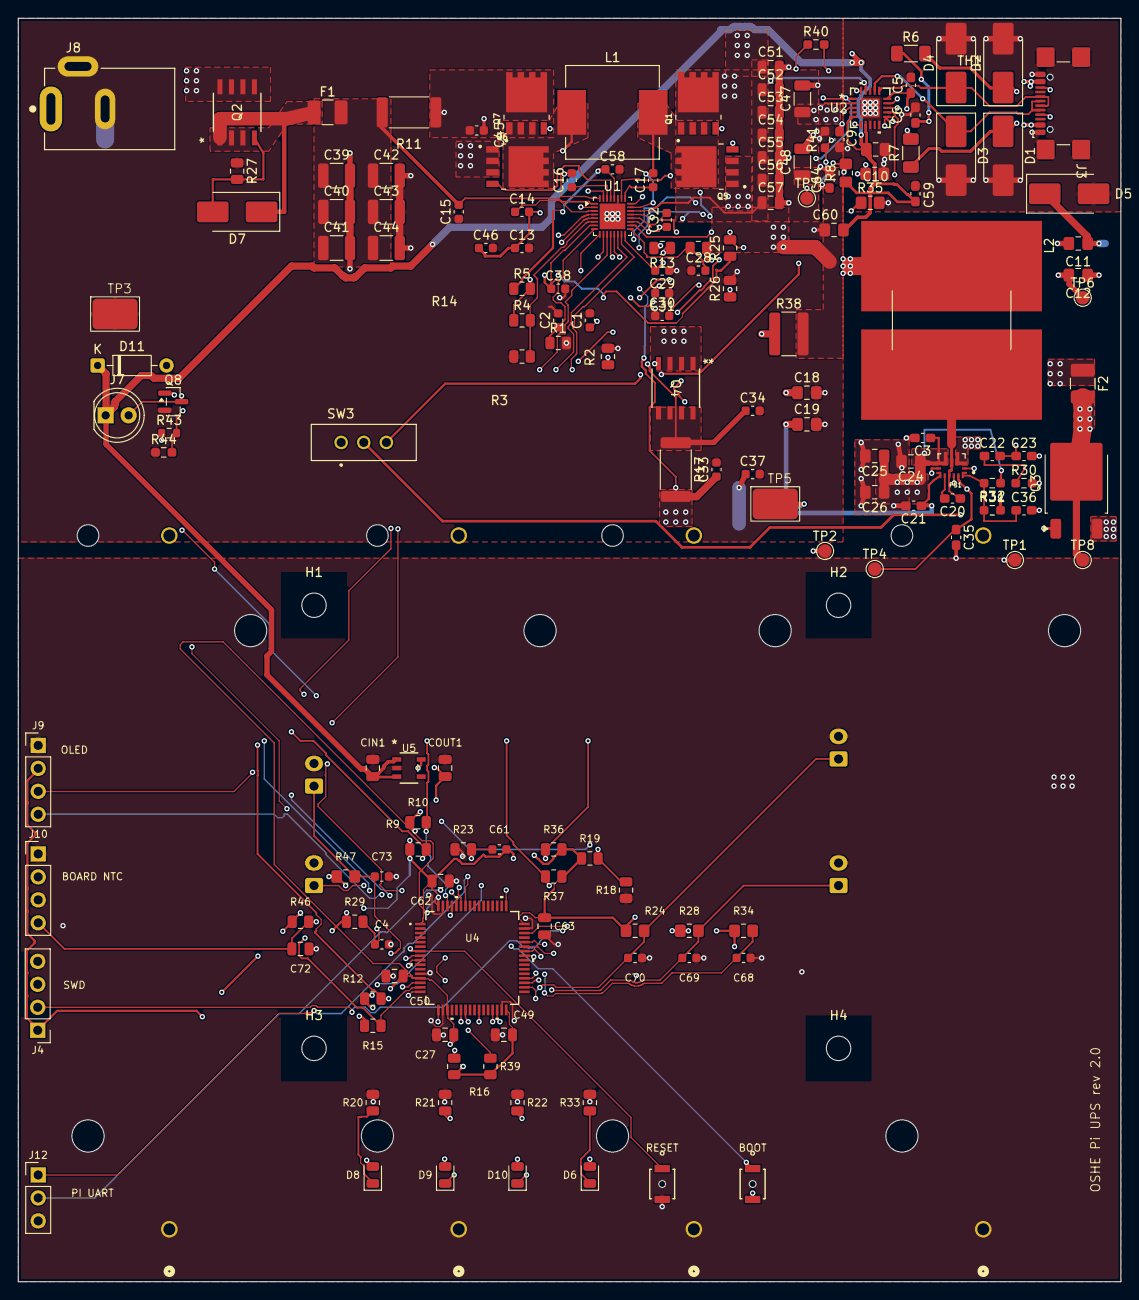
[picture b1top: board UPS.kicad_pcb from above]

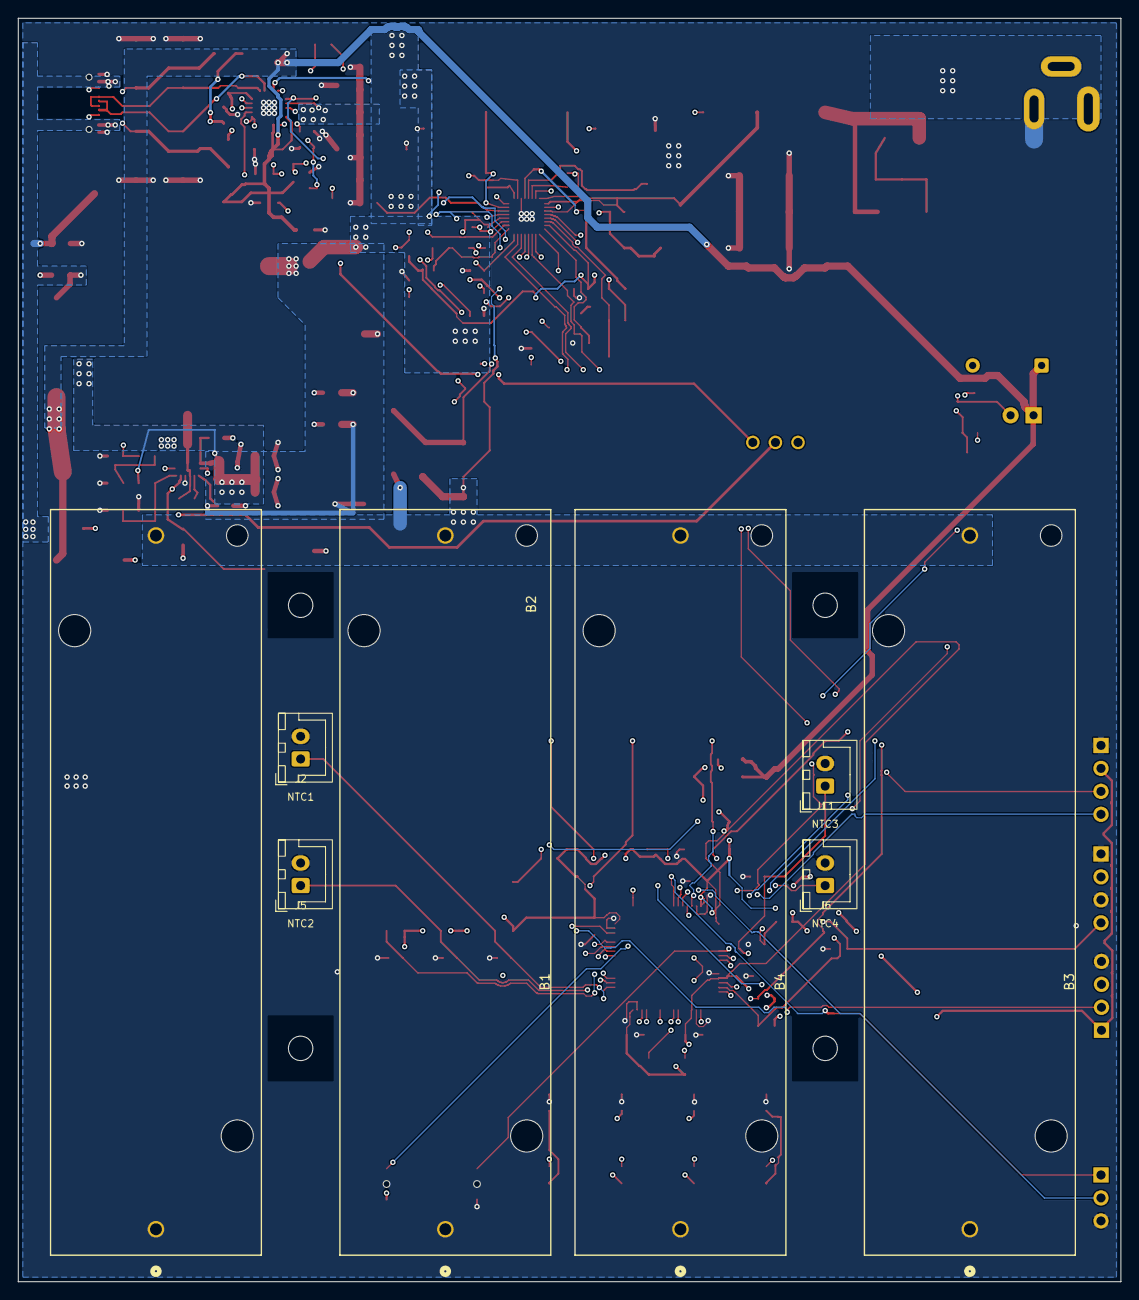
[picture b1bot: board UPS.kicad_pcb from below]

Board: 4 copper layers, 121.9 x 139.7 mm, 173 parts (8 on the bottom side), 85 nets.

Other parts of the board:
H1, H2, H3, H4: Pi5_M2.5_NPTH; MountingHole_2.7mm_M2.5

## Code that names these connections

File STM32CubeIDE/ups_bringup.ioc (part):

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Mcu.Name=STM32L152RCTx
Mcu.Package=LQFP64
Mcu.UserName=STM32L152RCTx
PA13.Mode=Serial_Wire
PA13.Signal=SYS_JTMS-SWDIO
PA14.Mode=Serial_Wire
PA14.Signal=SYS_JTCK-SWCLK
PA4.GPIOParameters=GPIO_Label
PA4.GPIO_Label=UNUSED_PA4
PA4.Signal=GPIO_Analog
PB8.Mode=I2C
PB8.Signal=I2C1_SCL
PB9.Mode=I2C
PB9.Signal=I2C1_SDA
PB13.GPIOParameters=GPIO_Label
PB13.GPIO_Label=BAT_TH1
PB13.Signal=GPIO_Analog
PB14.GPIOParameters=GPIO_Label
PB14.GPIO_Label=BAT_TH2
PB14.Signal=GPIO_Analog
PB15.GPIOParameters=GPIO_Label
PB15.GPIO_Label=BAT_TH4
PB15.Signal=GPIO_Analog
PB0.GPIOParameters=GPIO_Label,PinState
PB0.GPIO_Label=FAN_EN
PB0.PinState=GPIO_PIN_SET
PB0.Signal=GPIO_Output
PC0.GPIOParameters=GPIO_Label
PC0.GPIO_Label=BAT_TH3
PC0.Signal=GPIO_Analog
PC1.GPIOParameters=GPIO_Label
PC1.GPIO_Label=TEMP_BOARD
PC1.Signal=GPIO_Analog
RCC.HSE_VALUE=24000000
RCC.SYSCLKFreq_VALUE=2097000
board=custom

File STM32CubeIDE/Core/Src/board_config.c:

#include "board_config.h"

board_config_t board_config_make_phase1(I2C_HandleTypeDef *i2c)
{
  /* Centralize the phase-1 board assumptions so validation and firmware use one baseline. */
  board_config_t cfg = {
      .i2c = i2c,
      .bq25730_address_7bit = 0x6B,
      .mpq5031_address_7bit = 0x28,
      .startup_delay_ms = 15U,
      .run_poll_interval_ms = 250U,
      .fault_poll_interval_ms = 1000U,
      .bq_charge_voltage_mv = 4200U,
      .bq_charge_current_ma = 1000U,
      .bq_input_current_limit_ma = 3000U,
      .bq_input_voltage_limit_mv = 4608U,
      .bq_rac_milliohm = 10U,
      .bq_rsr_milliohm = 10U,
      .mpq_pdo1_current_ma = 5000U,
      .led_port = LED_GPIO_Port,
      .led_pin = LED_Pin,
      .prochot_port = PROCHOT_N_GPIO_Port,
      .prochot_pin = PROCHOT_N_Pin,
      .chrg_ok_port = CHRG_OK_GPIO_Port,
      .chrg_ok_pin = CHRG_OK_Pin,
      .vsel1_port = VSEL1_GPIO_Port,
      .vsel1_pin = VSEL1_Pin,
      .vsel2_port = VSEL2_GPIO_Port,
      .vsel2_pin = VSEL2_Pin,
  };

  return cfg;
}

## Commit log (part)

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2026-02-08 Add CAD files license
2026-02-08 Add PD IC and started USB C protection/bypass
2026-02-09 PD thermistor and more bypass caps
2026-02-09 Add diode footprints
2026-02-10 Updated Kicad_sym
2026-02-13 UPSOutput cleanup
2026-02-13 sym lib cleanup
2026-02-17 mcJohn
    STM32L152RCT6 schematic and CubeIDE project
2026-02-21 added components to bom
2026-02-21 Made Power Net Class and set up board parameters and constraints
2026-02-23 Moved most components where they belong-ish
    Barrel Jack's on the end as well as battery connector for now. The MOSFET's need to be really close to the caps in the charger module
2026-02-24 More PCB Progress, more to come tomorrow morning
2026-02-24 Last minute footprint fixes on charger module
2026-02-24 boot0 fix
2026-02-24 minor things
2026-02-24 Add thermistors for batteries and link signals
2026-02-24 found a short
2026-02-24 Start routing USB output on PCB
2026-02-24 Update PCB from schematic
2026-02-24 PCB Outline
2026-02-24 Add switch
2026-02-25 footprints?
2026-02-25 Output section of PCB
2026-02-25 Add extra via
2026-02-25 Random PCB cleanup
2026-02-25 Need to finish some traces, DRC warnings are keeping me from routing to the BQ,
2026-02-25 push button foot print
2026-02-25 replaced solder jumper with resistor
2026-02-25 Updated Footprints
2026-02-25 Did some routing, need to figure out how to route to BQ while appeasing DRC
2026-02-25 Ty's changes from this morning
2026-02-25 More PCB routing
2026-02-25 Implement I2C bring-up helpers in STM project
2026-02-26 Introduce fuses and a bit more routing
2026-02-26 More PCB Routing!!!!!
    Most of the MCU is done
2026-02-26 added vbat_sense to DAC
2026-02-26 last min pin rearangement
2026-02-26 VBATSENSE divider put in and some routing
    Little more routing, complete by tonight
2026-02-26 Ty's VBATSENSE Changes
    Let me know if I messed this part up, did a small amount
2026-02-26 More routing, almost done but Ty works til 5
2026-02-27 DRC is angry but everything has a route
    Angry about a lot of the vias in the top right specifically, there's A LOT of issues with clearance I want to look at, taking another break for now.
2026-02-28 Final board for now (Pre Spring Break)
2026-03-21 Remove cache and lock files
2026-03-23 ignore notes
2026-03-23 Add UPS supervisor bring-up firmware and validation tooling
